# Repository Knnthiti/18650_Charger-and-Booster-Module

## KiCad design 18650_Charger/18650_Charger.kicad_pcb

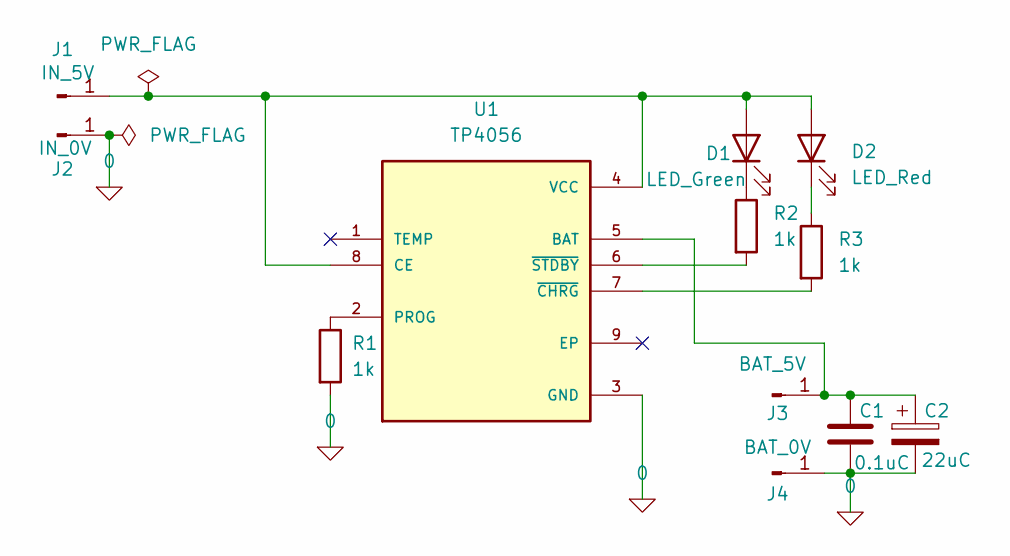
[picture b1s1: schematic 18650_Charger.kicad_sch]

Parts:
C1: 0.1uC; C_0805_2012Metric
C2: 22uC; CP_Radial_D5.0mm_P2.00mm
D1: LED_Green; LED_0603_1608Metric_Pad1.05x0.95mm_HandSolder
D2: LED_Red; LED_0603_1608Metric_Pad1.05x0.95mm_HandSolder
J1: IN_5V; PinHeader_1x01_P1.00mm_Vertical
J2: IN_0V; PinHeader_1x01_P1.00mm_Vertical
J3: BAT_5V; PinHeader_1x01_P1.00mm_Vertical
J4: BAT_0V; PinHeader_1x01_P1.00mm_Vertical
R1, R2, R3: 1k; LED_0603_1608Metric_Pad1.05x0.95mm_HandSolder
U1: TP4056; SOP127P600X175-9N

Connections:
0: C1.2, C2.2, J2.1, J4.1, R1.2, U1.3 (GND)
unnamed: D1.2 (A), D2.2 (A), J1.1, U1.4 (VCC), U1.8 (CE)
unnamed: D1.1 (K), R2.1
unnamed: D2.1 (K), R3.1
unnamed: C1.1, C2.1, J3.1, U1.5 (BAT)
unnamed: R1.1, U1.2 (PROG)
unnamed: R3.2, U1.7 (~CHRG)
unnamed: R2.2, U1.6 (~STDBY)

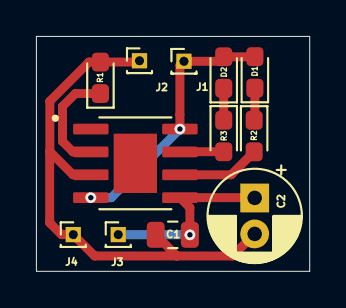
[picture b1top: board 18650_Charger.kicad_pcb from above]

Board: 2 copper layers, 15.2 x 13.0 mm, 12 parts (0 on the bottom side), 8 nets.

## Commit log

2026-01-31 FInish
2026-02-02 schemetic
2026-02-02 add T_sensor
2026-02-06 remove
2026-02-06 remove L
